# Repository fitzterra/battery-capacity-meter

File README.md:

Battery Capacity Meter
======================

**Table of Content**

1. [Introduction](#introduction)
2. [Components and software Stack](#components-and-software-stack)
3. [Project Layout](#project-layout)
4. [Firmware Development](#firmware-development)
	1. [Dev environment setup](#dev-environment-setup)
	2. [Flashing MicroPython](#flashing-micropython)
	3. [Submodules](#submodules)
	4. [Building and uploading firmware](#building-and-uploading-firmware)
		1. [Building](#building)
		2. [Uploading](#uploading)
	5. [Building docs](#building-docs)
5. [Documentation](#documentation)

Introduction
------------

This is a project to build something that can measure the capacity of
Lithium-Ion batteries, specifically 18650 cells, but not limited to those.

In order to fairly accurately measure the cell capacity, one has to do a full
discharge of the cell, and measure the energy used during the recharge. Or
alternatively, charge a fully discharged cell, measuring the energy used to get
battery to full capacity.

To get fairly accurate measurements from these techniques are more difficult
that it sounds due to some factors such as:

* Fully charged, or fully discharged are relative states. Unless whatever is
    used to accurately measure fully dis/charged state, there could be large
    variances.
* Unless the dis/charge cycle is done at a very high current rate, it could
    take a long time to fully dis/charge a cell of even a nominal capacity.
* Using large dis/charge currents is not the best way to measure capacity and
    may be more damaging than it needs to be.

To solve this, this meter has these features:

* Allows multiple (up to 4) batteries to be measured independently and
    concurrently.
* Uses known components and calibration to ensure that the fully dis/charged
    states are as close as the same at all times as possible.
* Does not use very large dis/charge currents to do the measurements.
* All dis/charge telemetry are streamed as MQTT data points to allow these to be
    captured in a separate system or database for further analysis - The
    **Battery Capacity Meter UI** project is a UI that evaluates these data
    points and record history and state for a collection of batteries.
* Each battery being measured is given, and expected to have, a unique ID that
    can be used to identify that battery in the telemetry as well as for
    keeping history.
* Allows singe charging, single discharging or full measurement cycles to be
    run per battery.
* A full measurement cycle will first charge the battery fully, then run 2
    (configurable) discharge and then charge cycles.

Components and software Stack
-----------------------------

* ESP32
* Micropython
* ADC ???
* OLED
* Encoder
* TP4056 Breakout
* KiCAD
* Black
* Pylint

Project Layout
--------------

The project contains the hardware sources (schematics, PCB, etc.), firmware
sources, docs, etc. The base structure is:

    ├── doc
    │   ├── design              - Firmware state diagrams, etc.
    │   ├── Electronics         - Schematics, etc in SVG or image format
    │   └── firmware-api        - Firmware auto generated docs - not versioned
    ├── Electronics
    │   └── BatCapMeter         - KiCad project for BC Meter and Controller
    └── Firmware
        ├── ScreenDesign        - Screen design images
        ├── src                 - Firmware source code dir
        │   ├── firmware        - Firmware build dir - not versioned
        │   ├── lib             - Various source libs
        │   ├── micropython_binary - MP binary will be downloaded here - not versioned
        │   ├── pydoctor_templates - Templates for auto HTML api doc building
        │   ├── runtime_conf    - Runtime config before uploading new firmware
        │   ├── testing         - Testing and demos for various libs - NOT testcases
        │   └── ui              - OLED+Rotary Encode UI library
        └── submodules          - All submodules used by the firmware
            ├── micropython-ads1x15
            ├── micropython-mqtt
            ├── micropython-stubs
            ├── micropython-tools
            ├── ssd1306_mp
            ├── ubutton
            └── uencoder

Firmware Development
--------------------

The BCM firmware is in the `Firmware/src` dir and this is the root dir for
development.

There are a number of moving parts to getting the development done, so as much
as possible is set up in a `Makefile` to help with this.

After setting the development environment up (see below), run `make help` to
see what make commands are available.

### Dev environment setup

The development environment also relies on a Python virtual environment to be
available.

The first thing to do is to ensure you set a `venv` up and make sure it is
activated when in the `Firmware/src` dir.

A very easy way to do this is by using [direnv]. This is normally very easy to
install in Linux and MacOS via your package manager or [Homebrew]. An `.envrc`
file for [direnv] is provided in `Firmware/.envrc`. Once you change into this
dir, you will be asked to allow this RC file, and it will set up an Python 3
virtual environment, as well as some other environment variables needed by the
`Makefile`.

You may have to adjust the `DEVICE_PORT` value in this `.envrc` to match the
device your board presents if it is not `/dev/ttyACM0` as the ESP32-S2 does on
Linux. Try `make detect-device` once your environment is set up and the device
is connected - YMMV.

If not using [direnv], make sure you have your own python virtual environment
set up and that the environment variables as in `Firmware/.envrc` are exported
when running any `make` command.

With all this done, run `make dev-env` to install all required Python packages
needed for firmware dev.

### Flashing MicroPython

The Micropython binary to flash to the ESP32 device is defined in the
`MCU_CONF` file.  
Please update this file is required, but this project is built around the Wemos
S2 Mini and all is set up for that device.

The version of the MP binary can be updated though. Look the `MP_DOWNLOAD_SITE`
config value for the download URL. Updated versions may be found there.

In order to get the S2 Mini into flash mode, press and delete both onboard
buttons at the same time. This is needed for all of the binary flash commands
(not needed for firmware flashing as described below).

If this is the first time flashing this device, then the flash first needs to
be erased with `make erase-flash`.

To flash the MP binary, do `make flash-bin`. If the MP binary is not already
downloaded, it will be downloaded from the download URL in the `MCU_CONF` file.

After flashing, reset the device by pressing the reset button.

Now the firmware can be flashed after making sure the submodules are set up.

### Submodules

The firmware uses a number of submodules for various bit of functionality.
These are `git submodules` and you must make sure all submodules have been
cloned. Do this with:

    git submodules sync
    git submodules udate --init

All submodules are cloned as their own repos under `Firmware/submodules`.

I order to include any parts of these submodules in the source, we simply
create symlinks from the submodule to the name we want for it in the source.
For example here are submodules symlinked in the `src/lib` dir:

    ads1x15.py -> ../../submodules/micropython-ads1x15/ads1x15.py
    led.py -> ../../submodules/micropython-tools/led.py
    mqtt_as.py -> ../../submodules/micropython-mqtt/mqtt_as/__init__.py
    ssd1306.py -> ../../submodules/ssd1306_mp/ssd1306.py
    ubutton.py -> ../../submodules/ubutton/ubutton.py
    uencoder.py -> ../../submodules/uencoder/uencoder.py

### Building and uploading firmware

After making sure the submodules are set up as described above, the firmware
can be built and uploaded as described below.

#### Building
This is done with the simple command: `make build`

The way this works is as follows:

* All the Python source files that will make up the final firmware are defined
    in the `MPY_SRC` list in the `Makefile`. If new files are added or others
    removed, this list **MUST** be updated.
* From this list, all source files will first be cross compiled in order to
    speed up runtime.
* As `make` is supposed to do, only changed sources files will be compiled if
    they have not been compiled before.
* All compiled files (`.mpy`) are placed in the `firmware` dir (which will be
    created if it does not exist, and is not versioned), using the same files
    structure as in the `src` dir.
* After this, `firmware` dir is now ready to be uploaded to the device.

#### Uploading

Once the firmware has been built, it can be uploaded.

This is done with `make upload`. Note that the upload target will also first
build any outdated firmware if run directly with having done a `make build`
first.

The firmware allows certain runtime configurations to be made via the OLED +
Encoder UI. These are effectively changes to any default config values and are
then saved in new runtime config files on the device.

In order to make sure **ONLY** the files in the firmware as built will be
placed on the device with the next firmware upload, the upload is a type of
file sync operation where any files not appearing in the built firmware folder,
are deleted from the device, while changed files are uploaded.

This sync operation also makes the uploads faster because only new and changed
compiled files are uploaded.

The problem is with the runtime configs. Since these are not part of the built
firmware, they are also deleted. This is not ideal while developing because
then any runtime config changes needs to be done after every firmware upload.

For this reason the `Makefile` has the `runtime-cfg-backup` target that will
look for any of these runtime config files on the device and copy them to
`runtime_conf/backup`.

The `upload` target has the `runtime-cfg-backup` target as dependency which
will then always first backup any runtime config files before doing the upload
sync. Afterwards, all runtime backups will then be copied back to the device.

To quickly get a REPL after changes were made to any files and an update is
needed, this flow is very useful:

    make upload repl

which will make a new build, backup runtime configs, upload only the changes,
restore runtime config and immediately connect to the device and start the REPL.

### Building docs

The source is extensively documented using Python docstrings. This allows
automatically generating a complete set of source and app documentation using
[pydoctor]

The [pydoctor] main setup is in the `pydoctor.ini` file with some additional
setup in the `docs` target in the `Makefile`.

To build the documentation, run `make docs` - this will show any doc errors,
and build the final static HTML docs in `doc/firmware-api/` from the top level
dir. In this dir will be an `index.html` file that can be opened directly in a
browser.

There is also a CI job for GitLab that will build the docs and make them
available as GitLab pages for the repo. See [Documentation](#Documentation)
below for more.

Documentation
-------------

The application is written in Micropython and the full app docs are available
[here](http://pages.gaul.za/gaulnet/battery-capacity-meter/)

<!-- links -->
[direnv]: https://github.com/direnv/direnv
[Homebrew]: https://brew.sh/
[pydoctor]: https://pydoctor.readthedocs.io

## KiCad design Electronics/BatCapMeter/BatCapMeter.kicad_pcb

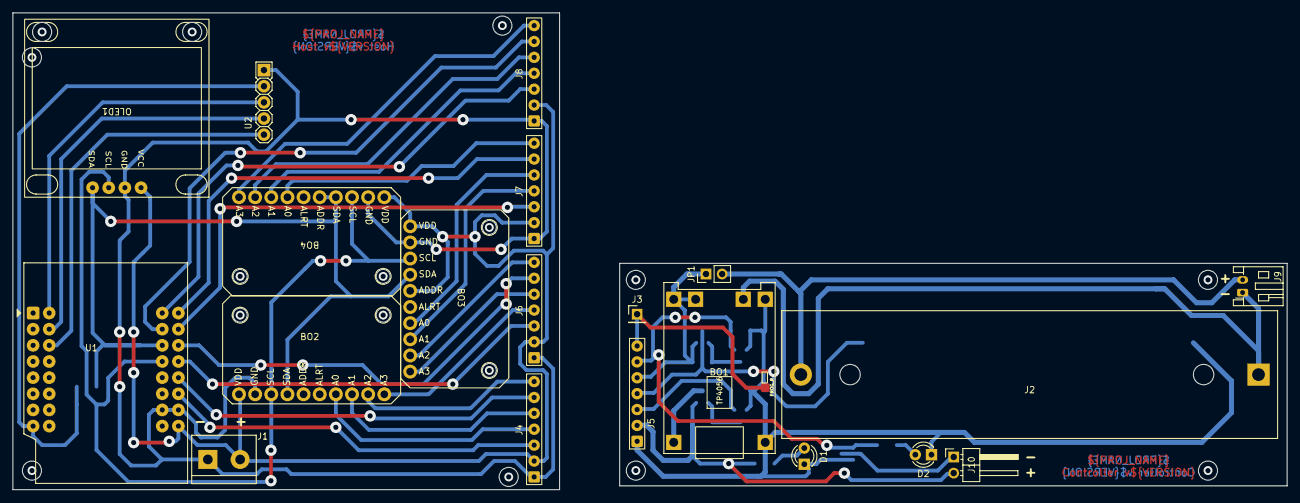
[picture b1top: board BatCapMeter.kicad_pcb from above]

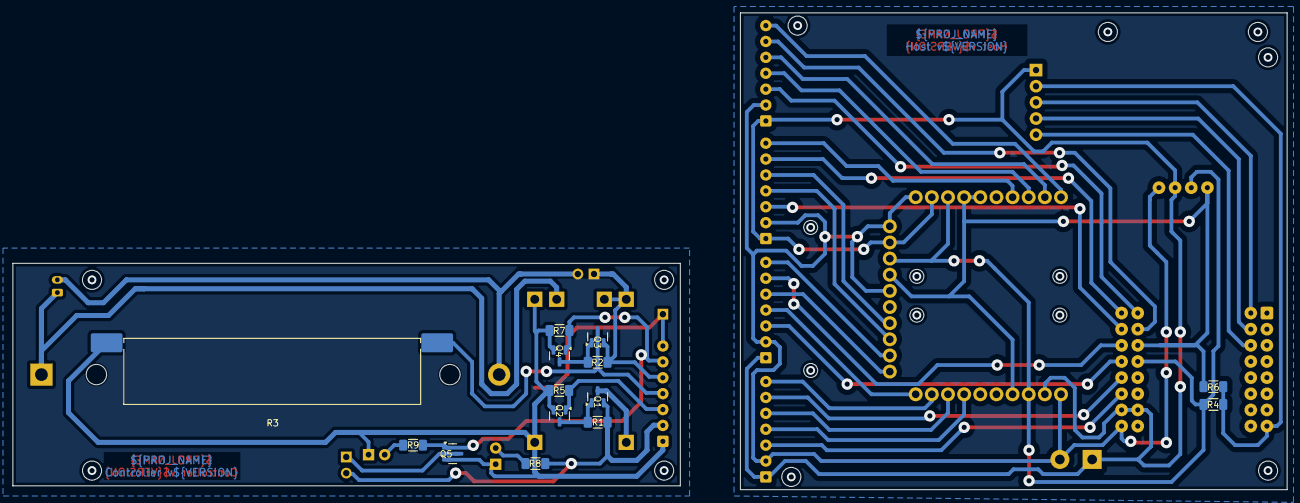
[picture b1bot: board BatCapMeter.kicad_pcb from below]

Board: 2 copper layers, 200.4 x 75.0 mm, 34 parts (14 on the bottom side), 43 nets.

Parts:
BO1: TP4056 BreakOut; TP4056_BreakOut_2
BO2, BO3, BO4: ADS1115_BO
D1: Power; LED_D3.0mm_Clear
D2: Discharge; LED_D3.0mm_Clear
J1: 5V Power; TerminalBlock_bornier-2_P5.08mm
J2: BatteryHolder; BatteryHolder_MPD_BH-18650-PC2
J3: R_PROG; PinHeader_1x01_P2.54mm_Vertical
J4: B0 Conn; SolderWire-1x07_P2.5mm_D0.8mm_OD1.8mm
J5: BCM Conn; SolderWire-1x07_P2.5mm_D0.8mm_OD1.8mm
J6: B1 Conn; SolderWire-1x07_P2.5mm_D0.8mm_OD1.8mm
J7: B2 Conn; SolderWire-1x07_P2.5mm_D0.8mm_OD1.8mm
J8: B3 Conn; SolderWire-1x07_P2.5mm_D0.8mm_OD1.8mm
J9: ExtBattery; JST_PH_S2B-PH-K_1x02_P2.00mm_Horizontal
J10: Fan; PinHeader_1x02_P2.54mm_Horizontal
JP1: Calib; PinHeader_1x02_P2.54mm_Vertical
OLED1: SSD13306_OLED_128x64-2_NonPad_Mounting_Holes
Q1, Q3: SI2301CDS; SOT-23
Q2, Q4, Q5: SI2302DDS; SOT-23
R1, R2, R4, R6: 10k; R_1206_3216Metric_Pad1.30x1.75mm_HandSolder
R3: Load; R_Axial_Power_L47.0mm_W10.0mm_P48.0mm_SMD
R5, R7: 12k; R_1206_3216Metric_Pad1.30x1.75mm_HandSolder
R8, R9: 5.1k; R_1206_3216Metric_Pad1.30x1.75mm_HandSolder
U1: WEMOS S2 Mini; WEMOS_S2_mini_NoKeepOut
U2: KY-040; KY-040-PORT

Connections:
/3V3: R4.1, R6.1, U1.8 (3V3), U2.VCC
/+5V: BO2.1 (VCC), BO3.1 (VCC), BO3.5 (ADDR), BO4.1 (VCC), J1.2, J4.2, J6.2, J7.2, J8.2, OLED1.1 (VCC), U1.9 (VBUS)
/B0_CH_C: BO2.9 (A2), J4.7
/B0_CH_CTL: J4.3, U1.11 (IO16)
/B0_DCH_C: BO2.7 (A0), J4.4
/B0_DCH_CTL: J4.6, U1.12 (IO18)
/B0_O+B_V: BO2.8 (A1), J4.5
/B1_CH_C: BO3.9 (A2), J6.7
/B1_CH_CTL: J6.3, U1.13 (IO33)
/B1_DCH_C: BO2.10 (A3), J6.4
/B1_DCH_CTL: J6.6, U1.14 (IO35)
/B1_O+B_V: BO3.10 (A3), J6.5
/B2_CH_C: BO4.7 (A0), J7.7
/B2_CH_CTL: J7.3, U1.15 (IO37)
/B2_DCH_C: BO3.8 (A1), J7.4
/B2_DCH_CTL: J7.6, U1.16 (IO39)
/B2_O+B_V: BO3.7 (A0), J7.5
/B3_CH_C: BO4.10 (A3), J8.7
/B3_CH_CTL: J8.3, U1.32 (IO40)
/B3_DCH_C: BO4.8 (A1), J8.4
/B3_DCH_CTL: J8.6, U1.31 (IO38)
/B3_O+B_V: BO4.9 (A2), J8.5
/BC_+5V: J5.2, J10.2, Q1.2 (S), R1.1, R8.1
/BC_CH_C: BO1.W1 (PROG), J3.1, J5.7
/BC_CH_CTL: J5.3, Q2.1 (G), R5.1
/BC_DCH_C: J5.4, Q3.3 (D), R3.1
/BC_DCH_CTL: J5.6, Q4.1 (G), Q5.1 (G), R7.1, R9.1
/BC_O+B_V: BO1.3 (Out+/B+), J5.5, JP1.1 (A), Q3.2 (S), R2.1
/ENC_CLK: U1.19 (IO4), U2.CLK
/ENC_DT: U1.18 (IO2), U2.DT
/ENC_SW: U1.17 (IO1), U2.SW
/SCL: BO2.3 (SCL), BO3.3 (SCL), BO4.3 (SCL), OLED1.3 (SCL), R4.2, U1.29 (IO34)
/SDA: BO2.4 (SDA), BO3.4 (SDA), BO4.4 (SDA), BO4.5 (ADDR), OLED1.4 (SDA), R6.2, U1.30 (IO36)
GND: BO2.2 (GND), BO3.2 (GND), BO4.2 (GND), J1.1, J4.1, J6.1, J7.1, J8.1, OLED1.2 (GND), U1.10 (GND), U1.26 (GND), U2.GND
GND1: BO1.2 (GND), D1.1 (K), D2.1 (K), J5.1, Q2.2 (S), Q4.2 (S), Q5.2 (S), R3.2, R5.2, R7.2
unnamed: BO1.4 (B-), J2.1, J9.1
unnamed: BO1.1 (Vin), Q1.3 (D)
unnamed: D1.2 (A), R8.2
unnamed: D2.2 (A), R9.2
unnamed: J2.2, J9.2, JP1.2 (B)
unnamed: J10.1, Q5.3 (D)
unnamed: Q1.1 (G), Q2.3 (D), R1.2
unnamed: Q3.1 (G), Q4.3 (D), R2.2

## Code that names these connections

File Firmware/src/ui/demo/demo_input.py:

"""
Demo for the UI Input module.
"""

import uasyncio as asyncio
from lib import ulogging as logging
from ui.ui_input import (
    input_evt,
    setupEncoder,
    EV_ROTATE,
    EV_BUTTON,
    DIR_CW,
    # DIR_CCW,
    SHORT_PRESS,
    # LONG_PRESS,
)
from config import (
    Pin,
    # i2c,
    ENC_CLK,
    ENC_DT,
    ENC_SW,
)


async def trackEncoder():
    """
    Shows Encoder events
    """
    logging.info("Starting encoder tracker...")
    e_type = e_val = None

    while True:
        logging.info("Waiting for encoder event...")
        await input_evt.wait()
        if input_evt.e_type == EV_ROTATE:
            e_type = "Rotate"
            e_val = "CW" if input_evt.e_val == DIR_CW else "CCW"
        elif input_evt.e_type == EV_BUTTON:
            e_type = "Button Press"
            e_val = "Short" if input_evt.e_val == SHORT_PRESS else "Long"
        else:
            logging.error(
                "Unknown even type: %s (with value: %s)",
                input_evt.e_type,
                input_evt.e_val,
            )
        logging.info(
            "Input event: %s (%s): %s (%s)",
            e_type,
            input_evt.e_type,
            e_val,
            input_evt.e_val,
        )
        input_evt.clear()


def demo():
    """
    Demo entry for UI Input.
    """
    logging.info("Setting up encoder...")
    # Set up the encoder
    setupEncoder(
        Pin(ENC_CLK, Pin.IN),
        Pin(ENC_DT, Pin.IN),
        Pin(ENC_SW, Pin.IN),
    )

    asyncio.run(trackEncoder())


if __name__ == "__main__":
    demo()

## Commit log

2024-10-05 Add initial Schematic and PCB layout
2024-10-06 Initial firmware setup
2024-10-12 Add some initial demos
2024-10-13 Add new Charge Controller
2024-10-13 Add ADC access and tracking to Charge Controller
2024-10-13 Update micropython-tools submodule
2024-10-20 Add UI package
2024-10-20 Add boot screen
2024-10-25 First menu
2024-10-26 Fix docs
2024-11-03 Charge controller features update
2024-11-09 Allow dynamic Menu entry names
2024-11-09 UI Menu: Allow fixed title
2024-11-09 Refactor Menu to Screen
2024-11-10 Base UI
2024-11-16 Allow network connection management
2024-11-16 BCMView: Battery ID - 2
2024-11-24 BMCView to start Charge/Discharge
2024-12-01 BCMView: Show charge and discharge progress
2024-12-28 Change to managing by State Machine
2024-12-29 MQTT braodcast support
2025-01-02 Add LICENSE
2025-01-02 Add site local config interfaces
2025-01-02 Doc Updates
2025-01-04 OLED UI Update
2025-01-04 Bump version for release
2025-01-04 Release v0.5.0
2025-01-18 SoC auto measure
2025-02-28 SoC Improvements
2025-02-28 Only publish Battery+ID messages on bat_v change
    Closes #41
2025-03-02 Use bat voltage on startup instead of 0V
2025-03-02 * Update UI Menu to allow a return item for a sub-menu
2025-03-02 * First commit for calibration
    - Add a Calibration menu under config
    - Add A Calibration screen to manage initial calibration sans saving.
2025-03-02 * Fix sitelocal_conf.updateLocal
    - The micropython version of `str.split` does not support a `maxsplit`
    arg.
2025-03-02 * Make the current monitor shut resistors calibrateable.
    - Add the new shunt config with support for site local configs
    - Update the main config to use this shunt config to set up the BC
    hardware.
    - Add functionality to the calibration screen to save site local shunt
    values per BC
2025-03-16 Improve telemetry emission
    * Telemetry emission periods are now more predicatble and does not
    depend on how many BCs are prsent
    * Telemetry outpur triggers from other parts of the system arealso
    improved.
2025-03-16 Release version 0.6.0
    Bump to v0.6.0 for release
2025-04-21 Add TODO on how to fix #44
2025-04-21 Update PCB Toner gen Makefile
    * Add option to generate an SMD placement pdf
2025-04-21 Update PCB to v1.1.0
    * Add a switch for a 5V fan on the controll PCB
    * Add a dischrage LED
2025-04-26 Add toner transfer PCB images
2025-04-26 Allow persistent config
2025-04-27 Emit logs as telemetry
2025-04-27 Prep for release v0.7.0
2025-04-27 Bump version to v0.7.0
2025-04-28 Update Toner Transfer PCB Layout
2025-04-28 More PCB layout updates.
2025-05-04 Add a calibration jumper
2025-05-04 Allow easier inter BC navigation
2025-05-04 Runtime configurable network settings
2025-05-04 Update README.md and added CI pipeline config
2025-05-04 Update CI pipeline for making docs
2025-05-04 Update .gitlab-ci.yml file
2025-05-10 Test allowing submodule cloning
2025-05-10 Fix submodule in ci/cd config
2025-05-10 Another fix for submodules in CI/CD config
2025-05-10 Debugging docs building
2025-05-10 More debugging...
2025-05-10 And more debugging...
2025-05-10 More debugging again...
2025-05-10 Updates to see if submodules will now work with gitlab HTPS
2025-05-10 Fix doc URL in README
2025-05-10 Dereference symlinks when copying app docs for pages.
2025-05-11 Remove old ADC tracker code
2025-05-11 Updates on .gitignore files with new micropython bin location
2025-05-11 Add a new config environment for the MCU device
2025-05-11 Makefile updates and cleanup
    * Add targets to download the correct Micropython binary as defined in
    MCU_CONF if not available.
    * Flash binary will now only flash for ESP32 and auto downloads the bin
    * Lots of cleanup in the Makefile
    Closes #50
2025-05-11 Extensive updates to README.md
2025-05-11 Release v0.8.0
2025-05-11 Release v0.8.0
    New release
2025-05-17 Move screen designs to doc dir
2025-05-17 Update and rename schematic image
2025-05-17 Move design dir
2025-05-17 Rename screen design dir
2025-05-17 Update firmware doc generation for GitLab pages
2025-05-17 Fox project URL for Firware API docs
2025-05-17 Fix remote URL for firmware docs when building for GL pages
2025-05-17 Fix stupid error in Makefile
2025-05-17 Hopefully the last fix for API docs project URL
2025-07-11 Small Fixes and Updates
2025-07-11 Prep for Release 0.9.0
2025-07-11 Bump version to 0.9.0
2025-07-12 Detect charged state when charge current falls to zero.
2025-07-12 Add release helper and make target
2025-07-12 Set version: v0.10.0_rc1
2025-07-12 Release 0.10.0
2025-07-12 Set version: v0.10.0
2025-08-02 Logging update for extra telemetry logging
2025-08-02 Set version: v0.11.0_rc1
2025-08-02 Release 0.11.0
2025-08-02 Set version: v0.11.0
2025-09-24 Documentation updates
2025-09-25 Handle large current drop on start charge
    Add functionality to handle large current drops on the start of charge
    of some batteries.
2025-09-26 Fix issues with large current drops on start charge
2025-09-26 Set version: v0.12.0_rc1
2025-09-26 Release 0.12.0
2025-09-26 Set version: v0.12.0
2025-09-27 Add reboot reason logger to boot.py
2025-09-27 Fix reset log writer to work with Micropython limitations
2025-09-27 Doc updates in boot.recordResetReason
2025-09-27 Add functions to return the reset cause log via MQTT
2025-09-27 Add a watchdog timer to guard against code freezes
2025-09-27 Add watchdog timer to guard against code freezes
2025-09-27 Set version: v0.13.0_rc1
2025-09-27 Release 0.13.0
2025-09-27 Set version: v0.13.0
2025-09-28 Log memory info
2025-09-28 Set version: v0.14.0_rc1
2025-09-28 Release 0.14.0
2025-09-28 Set version: v0.14.0
2025-09-28 Set version: v0.15.0_rc1
2025-10-18 Update documentation
2025-10-31 Add MCU Configs dir and symlink to MCU_CONF
2025-10-31 Fix import for UI demo
2025-11-09 Switch to UI submodule
    * Add the UI lib as a new submodule
    * Switch all libs and packages to use this new submodule
2025-11-09 Add a memory info log control
    * Add a config option to control if meme info is logged
    * Use this config option in the watchdog module
    * Also add a config manager for boolean config options that uses the new
    UI Toggle screen to toggle the option
    * Add a (hackey) config option for the mem info logger
2025-11-09 Set version: v0.15.0_rc2
2025-11-09 Release 0.15.0
2025-11-09 Set version: v0.15.0
2025-11-15 upgrade MQTT submodule
2025-11-22 Update ads1x15 submodule
2025-11-29 Update net_conn.connection
    * Update docs
    * Add a default function wide name identifier name
2025-12-06 Update net_conn and net_conf for network control
2025-12-06 Update aiomqttc submodule
2025-12-06 Replace mqtt_as.py with aiomqttc.py
2025-12-06 Remove micropython-mqtt submodule
2025-12-06 Add my fork of the aiomqttc.py as a submodule
2025-12-06 Rename testing telem.py to telemetry.py
2025-12-06 Update to use new split netconf and aiomqtt
2025-12-06 Set version: v0.15.0_rc3
2025-12-06 fix version
2025-12-06 Set version: v0.16.0_rc1
2025-12-07 Start network and mqManager in main and not in telemetry
2025-12-07 Add screen saver to all screens
2025-12-07 Update to latest UI submodule
2025-12-07 Set version: v0.16.0_rc2
2025-12-07 Update UI submodule
2025-12-07 Docs update
2025-12-07 Set version: v0.16.0_rc3
2025-12-07 Release 0.16.0
2025-12-07 Set version: v0.16.0
